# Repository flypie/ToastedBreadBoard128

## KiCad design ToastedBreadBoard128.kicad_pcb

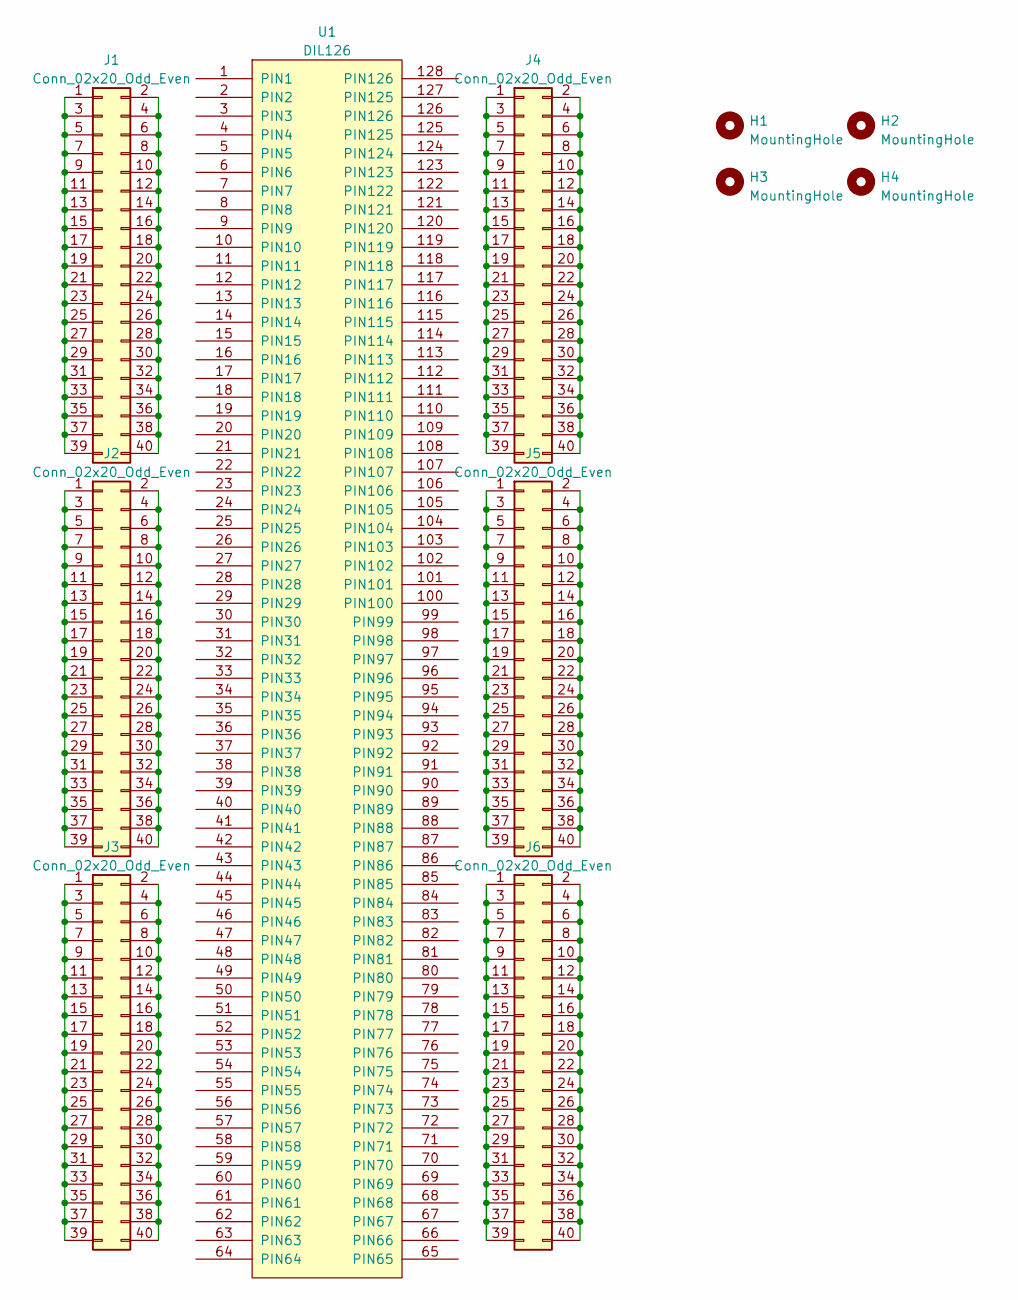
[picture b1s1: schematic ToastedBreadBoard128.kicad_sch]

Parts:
H1, H2, H3, H4: MountingHole; MountingHole_3.5mm_with_Stencil_hole
J1, J2, J3, J4, J5, J6: Conn_02x20_Odd_Even; PinHeader_2x20_P2.54mm_Vertical
U1: DIL126; DIP-128

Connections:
unnamed: J1.1, J1.3, J1.5, J1.7, J1.9, J1.11, J1.13, J1.15, J1.17, J1.19, J1.21, J1.23, J1.25, J1.27, J1.29, J1.31, J1.33, J1.35, J1.37, J1.39
unnamed: J1.2, J1.4, J1.6, J1.8, J1.10, J1.12, J1.14, J1.16, J1.18, J1.20, J1.22, J1.24, J1.26, J1.28, J1.30, J1.32, J1.34, J1.36, J1.38, J1.40
unnamed: J2.1, J2.3, J2.5, J2.7, J2.9, J2.11, J2.13, J2.15, J2.17, J2.19, J2.21, J2.23, J2.25, J2.27, J2.29, J2.31, J2.33, J2.35, J2.37, J2.39
unnamed: J2.2, J2.4, J2.6, J2.8, J2.10, J2.12, J2.14, J2.16, J2.18, J2.20, J2.22, J2.24, J2.26, J2.28, J2.30, J2.32, J2.34, J2.36, J2.38, J2.40
unnamed: J3.1, J3.3, J3.5, J3.7, J3.9, J3.11, J3.13, J3.15, J3.17, J3.19, J3.21, J3.23, J3.25, J3.27, J3.29, J3.31, J3.33, J3.35, J3.37, J3.39
unnamed: J3.2, J3.4, J3.6, J3.8, J3.10, J3.12, J3.14, J3.16, J3.18, J3.20, J3.22, J3.24, J3.26, J3.28, J3.30, J3.32, J3.34, J3.36, J3.38, J3.40
unnamed: J4.1, J4.3, J4.5, J4.7, J4.9, J4.11, J4.13, J4.15, J4.17, J4.19, J4.21, J4.23, J4.25, J4.27, J4.29, J4.31, J4.33, J4.35, J4.37, J4.39
unnamed: J4.2, J4.4, J4.6, J4.8, J4.10, J4.12, J4.14, J4.16, J4.18, J4.20, J4.22, J4.24, J4.26, J4.28, J4.30, J4.32, J4.34, J4.36, J4.38, J4.40
unnamed: J5.1, J5.3, J5.5, J5.7, J5.9, J5.11, J5.13, J5.15, J5.17, J5.19, J5.21, J5.23, J5.25, J5.27, J5.29, J5.31, J5.33, J5.35, J5.37, J5.39
unnamed: J5.2, J5.4, J5.6, J5.8, J5.10, J5.12, J5.14, J5.16, J5.18, J5.20, J5.22, J5.24, J5.26, J5.28, J5.30, J5.32, J5.34, J5.36, J5.38, J5.40
unnamed: J6.1, J6.3, J6.5, J6.7, J6.9, J6.11, J6.13, J6.15, J6.17, J6.19, J6.21, J6.23, J6.25, J6.27, J6.29, J6.31, J6.33, J6.35, J6.37, J6.39
unnamed: J6.2, J6.4, J6.6, J6.8, J6.10, J6.12, J6.14, J6.16, J6.18, J6.20, J6.22, J6.24, J6.26, J6.28, J6.30, J6.32, J6.34, J6.36, J6.38, J6.40

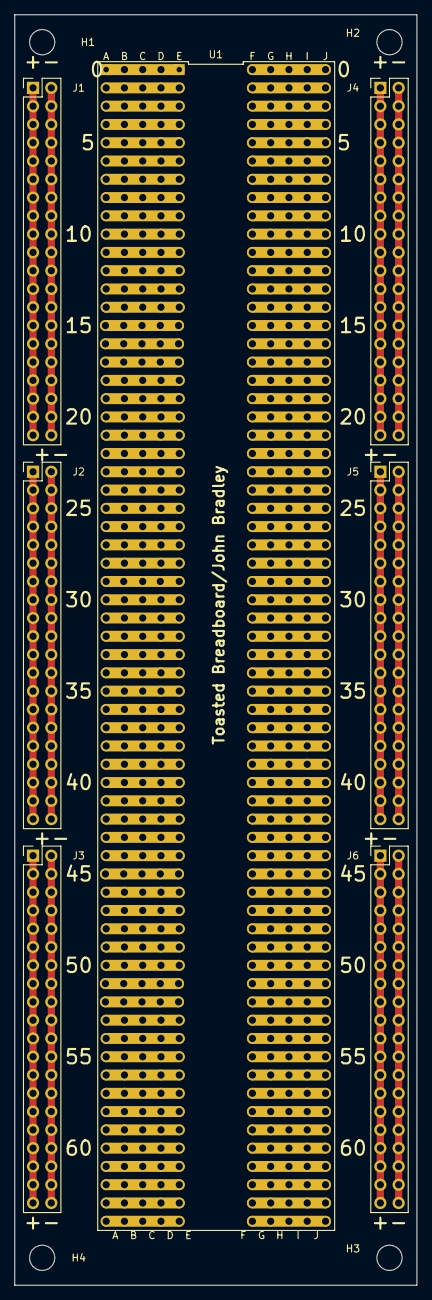
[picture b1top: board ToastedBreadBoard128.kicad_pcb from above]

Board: 2 copper layers, 55.9 x 176.5 mm, 11 parts (0 on the bottom side), 12 nets.

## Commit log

2024-03-14 Make all holes the same size.
2024-03-17 Correct Width.
2024-03-17 Add ignore.
